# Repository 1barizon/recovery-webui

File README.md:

# Recovery WebUI

Sistema de rastreamento e recuperação em tempo real para foguetes experimentais, desenvolvido para monitorar telemetria via comunicação serial LoRa e visualizar dados em interface web.

## 📋 Visão Geral

O Recovery WebUI é uma aplicação Flask que fornece uma interface web para monitoramento em tempo real de foguetes experimentais. O sistema recebe dados de telemetria via comunicação serial (tipicamente através de módulos LoRa), processa as informações e as exibe em um mapa interativo, permitindo o rastreamento da posição, altitude, e outros parâmetros importantes durante o voo.

### Funcionalidades Principais

- 🗺️ **Visualização em Mapa Interativo**: Mapa com múltiplas camadas (Google Satélite, Google Streets, OpenStreetMap)
- 🧊 **Visualizador 3D de Orientação**: Modelo 3D (cubo para satélite, foguete para foguetes) que gira conforme os dados IMU (giroscópio + acelerômetro)
- 📡 **Rastreamento em Tempo Real**: Comunicação via WebSocket para atualizações instantâneas
- 📊 **Registro de Dados**: Armazenamento automático de telemetria em formato CSV
- 🚀 **Suporte Dual**: Rastreamento simultâneo de foguete (#100) e satélite (#261)
- 📈 **Histórico de Voo**: Tabelas com histórico completo de dados recebidos
- 🔌 **Comunicação Serial**: Integração com dispositivos via porta serial (LoRa)

### Dados Monitorados

#### Foguete (TEAM_ID #100)

- Posição GPS (latitude, longitude)
- Altitude barométrica
- Número de satélites GPS
- Status do paraquedas
- RSSI (intensidade do sinal)

#### Satélite (TEAM_ID #261)

- Posição GPS (latitude, longitude)
- Altitude
- Temperatura
- Umidade relativa
- Pressão atmosférica
- Número de satélites GPS
- RSSI (intensidade do sinal)

## 🚀 Início Rápido

### Pré-requisitos

- Python 3.7 ou superior
- Porta serial disponível (para comunicação com o módulo LoRa)
- Navegador web moderno

### Instalação

1. Clone o repositório:

```bash
git clone <url-do-repositorio>
cd recovery-webui
```

2. Instale as dependências:

```bash
pip install -r requirements.txt
```

### Uso

1. Conecte o módulo LoRa receptor ao computador via USB

2. Execute a aplicação:

```bash
cd app
python app.py
```

3. Selecione a porta serial quando solicitado:

```
Portas seriais disponíveis:
1: /dev/ttyACM0
2: /dev/ttyUSB0
Selecione a porta serial (número): 1
```

4. O navegador abrirá automaticamente em `http://localhost:5000`

5. Acesse as diferentes visualizações:
   - `/` - Dados do foguete principal
   - `/satellite` - Dados do satélite
   - `/visualizador3d` - Orientação 3D (cubo/foguete)

## 📁 Estrutura do Projeto

```
recovery-webui/
├── app/
│   ├── app.py              # Aplicação Flask principal
│   ├── module/
│   │   ├── __init__.py
│   │   └── SerialCOM.py    # Módulo de comunicação serial
│   ├── static/
│   │   ├── css/            # Estilos
│   │   └── js/
│   │       └── app.js      # Lógica do cliente (WebSocket, mapa)
│   ├── templates/
│   │   ├── base.html       # Template base
│   │   ├── index.html      # Página do foguete
│   │   └── satellite.html  # Página do satélite
│   └── logs/
│       └── log.csv         # Logs de telemetria
├── requirements.txt        # Dependências Python
└── README.md              # Este arquivo
```

## 🛠️ Tecnologias Utilizadas

### Backend

- **Flask** - Framework web Python
- **Flask-SocketIO** - Comunicação WebSocket em tempo real
- **PySerial** - Comunicação serial com hardware

### Frontend

- **Leaflet.js** - Biblioteca de mapas interativos
- **Socket.IO** - Cliente WebSocket
- **jQuery** - Manipulação do DOM
- **Font Awesome** - Ícones

## 📡 Protocolo de Comunicação

O sistema espera dados no seguinte formato CSV via serial:

```
TEAM_ID,millis,count,altp,temp,umi,p,gp,gr,gy,ap,ar,ay,hora,data,alt,lat,lon,sat,rssi
```

Onde:

- `TEAM_ID`: Identificador do dispositivo (#100 para foguete, #261 para satélite)
- `millis`: Tempo em milissegundos desde o boot
- `count`: Contador de pacotes
- `altp`: Altitude barométrica
- `temp`: Temperatura (°C)
- `umi`: Umidade relativa (%)
- `p`: Pressão atmosférica (hPa)
- `gp`, `gr`, `gy`: Dados do giroscópio (pitch, roll, yaw)
- `ap`, `ar`, `ay`: Dados do acelerômetro (x, y, z)
- `hora`, `data`: Hora e data do GPS
- `alt`: Altitude GPS (m)
- `lat`, `lon`: Coordenadas GPS
- `sat`: Número de satélites GPS

- `rssi`: Intensidade do sinal LoRa

## 📚 Documentação Adicional

Para informações mais detalhadas, consulte a pasta `docs/`:

- [Guia de Instalação](docs/installation.md) - Instalação detalhada e configuração
- [Arquitetura do Sistema](docs/architecture.md) - Detalhes técnicos da arquitetura
- [Documentação da API](docs/api.md) - Endpoints e eventos WebSocket
- [Guia de Desenvolvimento](docs/development.md) - Contribuindo para o projeto

## 🐛 Solução de Problemas

### Porta serial não encontrada

- Verifique se o dispositivo está conectado
- Em Linux, você pode precisar de permissões: `sudo usermod -a -G dialout $USER`
- Verifique se o driver CH340/CP2102 está instalado (dependendo do módulo)

### Dados não aparecem no mapa

- Verifique se o formato dos dados serial está correto
- Confira o console do navegador (F12) para erros JavaScript
- Verifique os logs do servidor no terminal

### Navegador não abre automaticamente

- Abra manualmente: `http://localhost:5000`
- Verifique se a porta 5000 não está em uso

## 🤝 Contribuindo

Contribuições são bem-vindas! Por favor:

1. Faça um fork do projeto
2. Crie uma branch para sua feature (`git checkout -b feature/MinhaFeature`)
3. Commit suas mudanças (`git commit -m 'Adiciona MinhaFeature'`)
4. Push para a branch (`git push origin feature/MinhaFeature`)
5. Abra um Pull Request

Leia nosso [Guia de Contribuição](CONTRIBUTING.md) para mais detalhes sobre padrões de código, processo de desenvolvimento e como reportar bugs.

## 📝 Licença

Este projeto é open source e está disponível para uso educacional e experimental.

## 🔗 Projetos Relacionados

- [flight-computer](../flight-computer) - Firmware do computador de bordo do foguete

## 📧 Contato

Para dúvidas ou sugestões, abra uma issue no repositório.

---

Desenvolvido para competições e experimentos de foguetemodelismo 🚀

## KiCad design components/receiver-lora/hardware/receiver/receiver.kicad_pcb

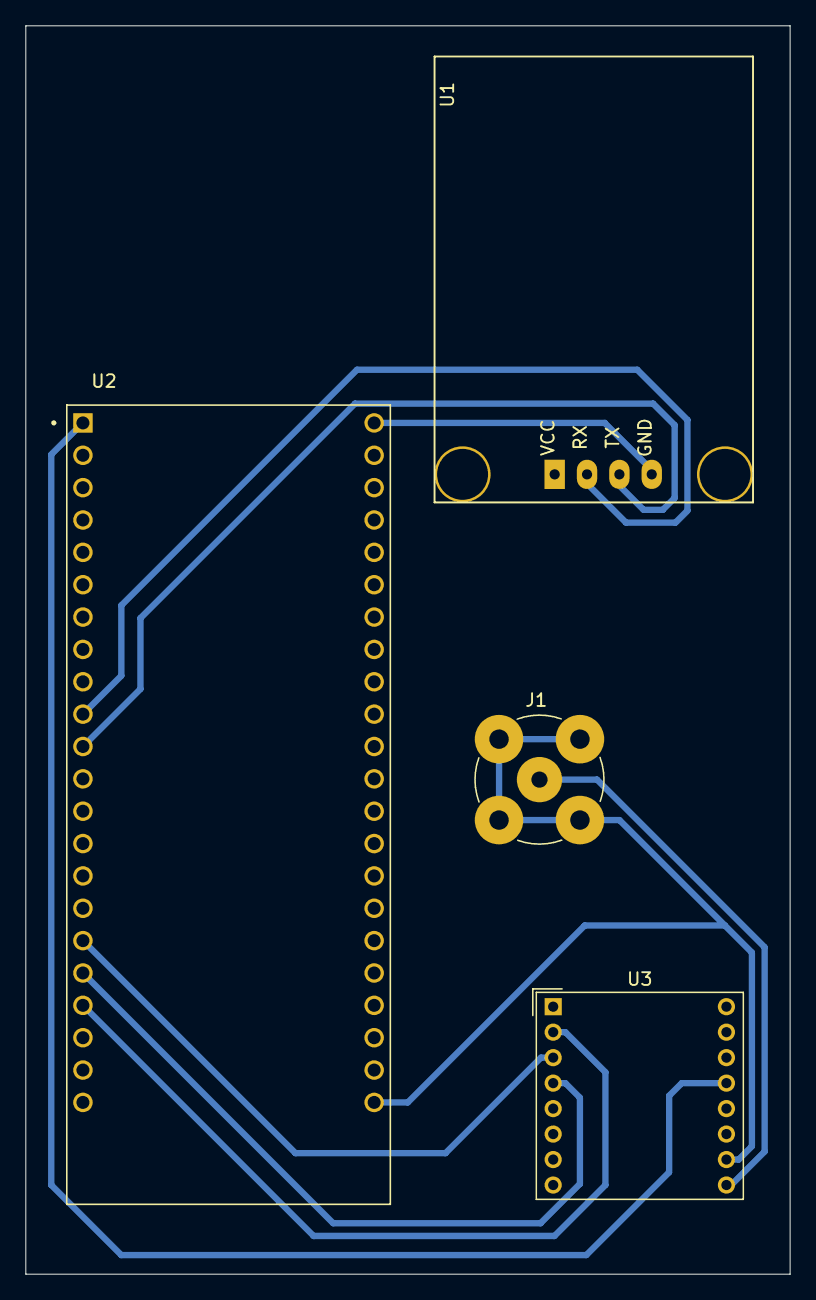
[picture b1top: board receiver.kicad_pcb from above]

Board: 2 copper layers, 60.0 x 98.0 mm, 4 parts (0 on the bottom side), 11 nets.

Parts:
J1: Conn_Coaxial_Small; BNC_TEConnectivity_1478204_Vertical
U1: GY-NEO6MV2
U2: ESP32-S3-DEVKITC-1-N8R8
U3: RFM95W-915S2; HOPERF_RFM9XW_THT

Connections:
/RFID_CS: U2.J1_16 (GPIO10), U3.5 (NSS)
/RFID_RST: U2.J1_15 (GPIO9), U3.6 (RESET)
/SPI_MISO: U2.J1_19 (GPIO13), U3.2 (MISO)
/SPI_MOSI: U2.J1_17 (GPIO11), U3.3 (MOSI)
/SPI_SCK: U2.J1_18 (GPIO12), U3.4 (SCK)
unnamed: J1.2 (Ext), U1.4 (GND), U2.J1_22 (GND3), U2.J3_1 (GND), U2.J3_21 (GND1), U2.J3_22 (GND2), U3.10 (GND)
unnamed: J1.1 (In), U3.9 (ANT)
unnamed: U1.2 (RX), U2.J1_10 (GPIO17)
unnamed: U1.3 (TX), U2.J1_11 (GPIO18)
unnamed: U1.1 (VCC), U2.J1_21 (5V0)
unnamed: U2.J1_1 (3V3), U3.13 (3.3V)

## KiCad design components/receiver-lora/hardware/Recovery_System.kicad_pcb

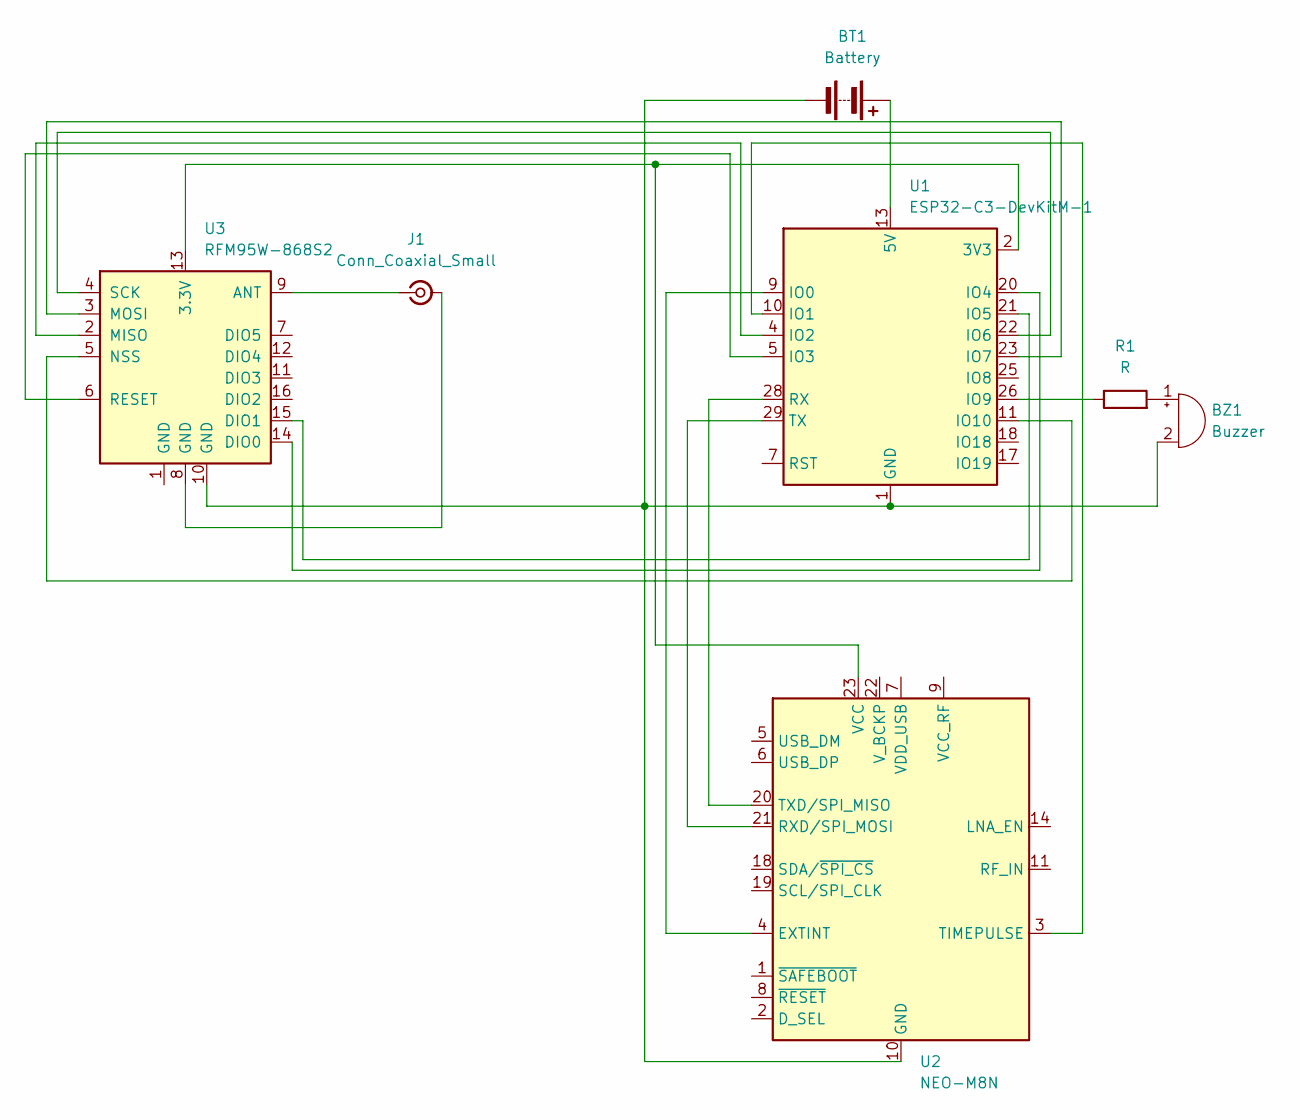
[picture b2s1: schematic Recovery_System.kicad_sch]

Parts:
BT1: Battery; JST_PH_B2B-PH-K_1x02_P2.00mm_Vertical
BZ1: Buzzer; Buzzer_TDK_PS1240P02BT_D12.2mm_H6.5mm
J1: Conn_Coaxial_Small; SMA_Samtec_SMA-J-P-H-ST-EM1_EdgeMount
R1: R; R_0603_1608Metric
U1: ESP32-C3-DevKitM-1
U2: NEO-M8N; ublox_NEO
U3: RFM95W-868S2; HOPERF_RFM9XW_SMD

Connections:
unnamed: BT1.1 (+), U1.13 (5V), U1.14 (5V)
unnamed: BT1.2 (-), BZ1.2 (-), U1.1 (GND), U1.6 (GND), U1.8 (GND), U1.12 (GND), U1.15 (GND), U1.16 (GND), U1.19 (GND), U1.24 (GND), U1.27 (GND), U1.30 (GND), U2.10 (GND), U2.12 (GND), U2.13 (GND), U2.24 (GND), U3.10 (GND)
unnamed: BZ1.1 (+), R1.2
unnamed: J1.2 (Ext), U3.8 (GND)
unnamed: J1.1 (In), U3.9 (ANT)
unnamed: U1.9 (IO0), U2.4 (EXTINT)
unnamed: U1.10 (IO1), U2.3 (TIMEPULSE)
unnamed: U1.4 (IO2), U3.2 (MISO)
unnamed: U1.5 (IO3), U3.6 (RESET)
unnamed: U1.20 (IO4), U3.14 (DIO0)
unnamed: U1.21 (IO5), U3.15 (DIO1)
unnamed: U1.22 (IO6), U3.4 (SCK)
unnamed: U1.23 (IO7), U3.3 (MOSI)
unnamed: R1.1, U1.26 (IO9)
unnamed: U1.11 (IO10), U3.5 (NSS)
unnamed: U1.28 (RX), U2.20 (TXD/SPI_MISO)
unnamed: U1.29 (TX), U2.21 (RXD/SPI_MOSI)
unnamed: U1.2 (3V3), U1.3 (3V3), U2.23 (VCC), U3.13 (3.3V)

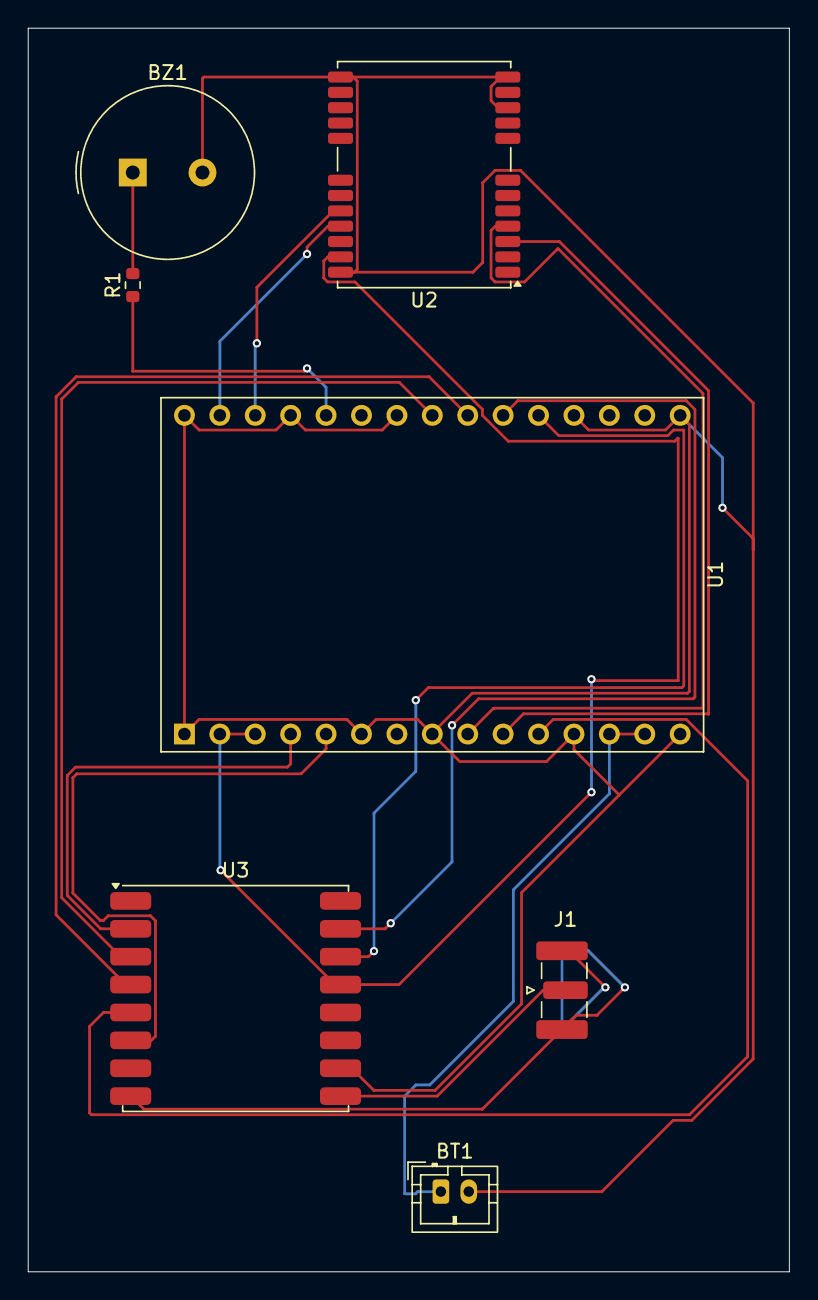
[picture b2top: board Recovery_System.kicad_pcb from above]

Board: 2 copper layers, 54.6 x 89.2 mm, 7 parts (0 on the bottom side), 18 nets.

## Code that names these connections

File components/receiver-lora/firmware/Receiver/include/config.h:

#pragma once

/* ================================================================
   Ground Station — Configuração central
   Pinagem conforme esquemático KiCad (ESP32-C3-DevKitM-1)
   ================================================================ */

// ── LoRa RFM95W-868S2 (SPI) ──────────────────────────────────
//  Pinagem conforme esquemático KiCad (U3 → U1 ESP32-C3)
#define SS_LORA    10   // NSS   → IO10
#define RST_LORA    3   // RESET → IO3
#define DIO0_LORA   4   // DIO0  → IO4

//  SPI explícito — obrigatório no ESP32-C3 (sem pinos SPI default)
#define SPI_SCK     6   // SCK   → IO6
#define SPI_MOSI    7   // MOSI  → IO7
#define SPI_MISO    2   // MISO  → IO2

#define LORA_FREQ  868E6  // Hz — igual ao foguete/satélite
#define SYNC_WORD  0xF3   // Igual ao foguete/satélite

// ── GPS NEO-M8N (Serial1) ────────────────────────────────────
//  TXD do GPS vai no RX do ESP32 e vice-versa
#define RX_GPS     28   // TXD NEO-M8N → IO28 ESP32-C3
#define TX_GPS     29   // RXD NEO-M8N → IO29 ESP32-C3

// ── Buzzer ───────────────────────────────────────────────────
#define BUZZER_PIN  9

// ── Serial USB → Recovery WebUI ──────────────────────────────
#define SERIAL_BAUD 115200

// ── IDs dos dispositivos monitorados ─────────────────────────
#define TEAM_ID_ROCKET    "#100"
#define TEAM_ID_SATELLITE "#261"

// ── Intervalo de emissão do GPS da ground station (ms) ───────
#define GPS_EMIT_INTERVAL 2000

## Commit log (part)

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2026-02-12 docs: add docs/ and files
2026-05-08 refactor: reorganize repository structure for Ground Station expansion
2026-05-08 docs: update paths after repository reorganization
2026-05-08 Chore: Remove useless files
2026-05-15 Create temp
2026-05-15 Create mi
2026-05-15 Add new 'mi' component
2026-05-16 Update greeting from 'Hello' to 'Goodbye'
2026-05-16 Update active layer and net inspector settings
2026-05-16 Update print statement from 'Hello' to 'Goodbye'
2026-05-16 Add pinout reference for ESP32-C3 and peripherals
    Added detailed pinout reference for ESP32-C3-DevKIT-1, RFM95W-868S2, and NEO-M8N modules, including power and design rules.
2026-05-18 Modify net connections and add resistor and buzzer
    Updated net connections and added new components including a resistor and a buzzer with their properties.
2026-05-20 Add diff pair dimensions, track widths, and via dimensions
2026-05-20 Change active layer from 25 to 0 in Recovery_System
2026-06-17 Update Buzzer.h with new initialization and beep functions
    Refactored buzzer functions and added new beep patterns.
2026-06-17 Refactor LoRa and GPS configuration settings
2026-06-17 Refactor Buzzer functions and update signal handling
2026-06-17 Refactor includes and class names in main.cpp
